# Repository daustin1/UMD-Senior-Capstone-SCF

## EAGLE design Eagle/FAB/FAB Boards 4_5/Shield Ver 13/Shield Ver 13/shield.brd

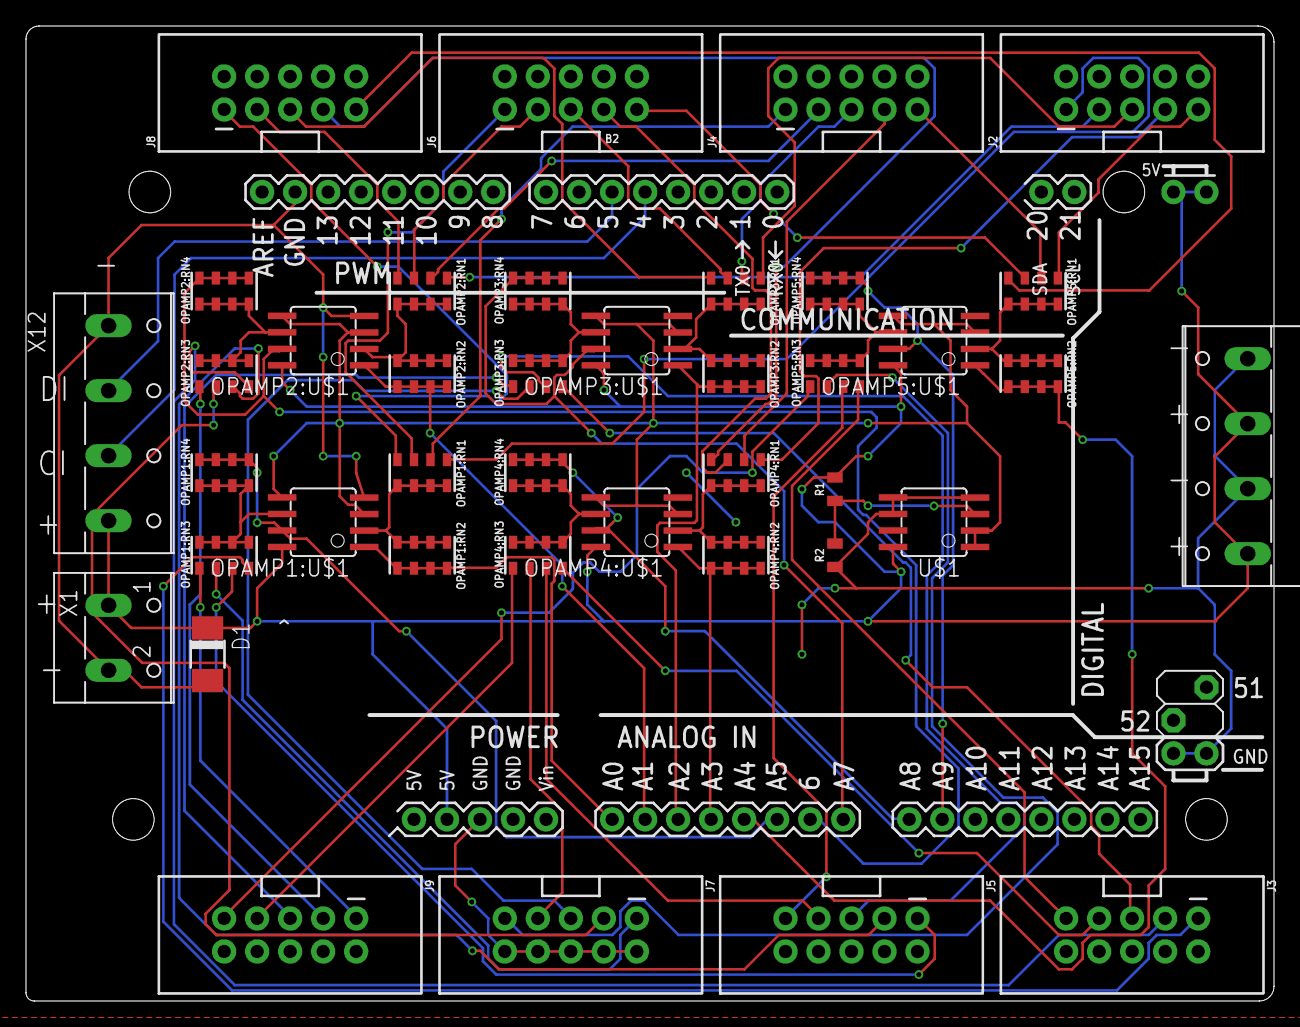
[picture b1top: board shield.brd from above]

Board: 2 copper layers, 96.0 x 75.0 mm, 41 parts (0 on the bottom side), 66 nets.

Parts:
B2: ARDUINO_MEGA_R3_EDITARDUINO_MEGA_EDIT; ARDUINO_MEGA_EDIT
D1: DO-214AC
J2, J3, J4, J5, J6, J7, J8, J9: AVR_SPI_PROG_5X2_NEWPTH2; 2X5-SHROUDED
OPAMP1:RN1, OPAMP1:RN2, OPAMP1:RN3, OPAMP1:RN4, OPAMP2:RN1, OPAMP2:RN2, OPAMP2:RN3, OPAMP2:RN4, OPAMP3:RN1, OPAMP3:RN2, OPAMP3:RN3, OPAMP3:RN4, OPAMP4:RN1, OPAMP4:RN2, OPAMP4:RN3, OPAMP4:RN4, OPAMP5:RN1, OPAMP5:RN2, OPAMP5:RN3, OPAMP5:RN4: 10k; 0805-ARV_EDIT10K
OPAMP1:U$1, OPAMP2:U$1, OPAMP3:U$1, OPAMP4:U$1, OPAMP5:U$1: MCP6002SMT; SOIC8
R1, R2: 1k; 0805
U$1: MCP6002SMT; SOIC8
X1: W237-102
X11, X12: W237-4

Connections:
+5V: B2.5V@0, B2.5V@1, B2.5V@2, D1.C, OPAMP1:U$1.8, OPAMP2:U$1.8, OPAMP3:U$1.8, OPAMP4:U$1.8, OPAMP5:U$1.8, R1.2, U$1.8, X1.1, X11.1, X11.3, X12.4
A1O: B2.A0, OPAMP1:RN2.5, OPAMP1:RN2.6, OPAMP1:RN2.7, OPAMP1:RN2.8, OPAMP1:U$1.1
A2O: B2.A1, OPAMP2:RN2.5, OPAMP2:RN2.6, OPAMP2:RN2.7, OPAMP2:RN2.8, OPAMP2:U$1.1
A3O: B2.A2, OPAMP3:RN2.5, OPAMP3:RN2.6, OPAMP3:RN2.7, OPAMP3:RN2.8, OPAMP3:U$1.1
A4O: B2.A3, OPAMP4:RN2.5, OPAMP4:RN2.6, OPAMP4:RN2.7, OPAMP4:RN2.8, OPAMP4:U$1.1
A5O: B2.A4, OPAMP5:RN2.5, OPAMP5:RN2.6, OPAMP5:RN2.7, OPAMP5:RN2.8, OPAMP5:U$1.1
A6O: B2.A5, OPAMP1:RN4.5, OPAMP1:RN4.6, OPAMP1:RN4.7, OPAMP1:RN4.8, OPAMP1:U$1.7
A7O: B2.A6, OPAMP2:RN4.5, OPAMP2:RN4.6, OPAMP2:RN4.7, OPAMP2:RN4.8, OPAMP2:U$1.7
A8O: B2.A7, OPAMP3:RN4.5, OPAMP3:RN4.6, OPAMP3:RN4.7, OPAMP3:RN4.8, OPAMP3:U$1.7
A9O: B2.A8, OPAMP4:RN4.5, OPAMP4:RN4.6, OPAMP4:RN4.7, OPAMP4:RN4.8, OPAMP4:U$1.7
A10O: B2.A9, OPAMP5:RN4.5, OPAMP5:RN4.6, OPAMP5:RN4.7, OPAMP5:RN4.8, OPAMP5:U$1.7
CI: B2.4, X12.3
DI: B2.5, X12.2
GND: B2.GND@0, B2.GND@1, B2.GND@2, B2.GND@3, B2.GND@4, D1.A, J2.2, J2.4, J2.6, J2.8, J2.10, J3.2, J3.4, J3.6, J3.8, J3.10, J4.2, J4.4, J4.6, J4.8, J4.10, J5.2, J5.4, J5.6, J5.8, J5.10, J6.2, J6.4, J6.6, J6.8, J6.10, J7.2, J7.4, J7.6, J7.8, J7.10, J8.2, J8.4, J8.6, J8.8, J8.10, J9.2, J9.4, J9.6, J9.8, J9.10, OPAMP1:U$1.4, OPAMP2:U$1.4, OPAMP3:U$1.4, OPAMP4:U$1.4, OPAMP5:U$1.4, R2.1, U$1.4, U$1.5, U$1.6, X1.2, X11.2, X11.4, X12.1
unnamed: R1.1, R2.2, U$1.3
OPAMP1:N$1: OPAMP1:RN3.5, OPAMP1:RN3.6, OPAMP1:RN3.7, OPAMP1:RN3.8, OPAMP1:RN4.1, OPAMP1:RN4.2, OPAMP1:RN4.3, OPAMP1:RN4.4, OPAMP1:U$1.6
OPAMP1:N$2: OPAMP1:RN1.5, OPAMP1:RN1.6, OPAMP1:RN1.7, OPAMP1:RN1.8, OPAMP1:RN2.1, OPAMP1:RN2.2, OPAMP1:RN2.3, OPAMP1:RN2.4, OPAMP1:U$1.2
OPAMP2:N$1: OPAMP2:RN3.5, OPAMP2:RN3.6, OPAMP2:RN3.7, OPAMP2:RN3.8, OPAMP2:RN4.1, OPAMP2:RN4.2, OPAMP2:RN4.3, OPAMP2:RN4.4, OPAMP2:U$1.6
OPAMP2:N$2: OPAMP2:RN1.5, OPAMP2:RN1.6, OPAMP2:RN1.7, OPAMP2:RN1.8, OPAMP2:RN2.1, OPAMP2:RN2.2, OPAMP2:RN2.3, OPAMP2:RN2.4, OPAMP2:U$1.2
OPAMP3:N$1: OPAMP3:RN3.5, OPAMP3:RN3.6, OPAMP3:RN3.7, OPAMP3:RN3.8, OPAMP3:RN4.1, OPAMP3:RN4.2, OPAMP3:RN4.3, OPAMP3:RN4.4, OPAMP3:U$1.6
OPAMP3:N$2: OPAMP3:RN1.5, OPAMP3:RN1.6, OPAMP3:RN1.7, OPAMP3:RN1.8, OPAMP3:RN2.1, OPAMP3:RN2.2, OPAMP3:RN2.3, OPAMP3:RN2.4, OPAMP3:U$1.2
OPAMP4:N$1: OPAMP4:RN3.5, OPAMP4:RN3.6, OPAMP4:RN3.7, OPAMP4:RN3.8, OPAMP4:RN4.1, OPAMP4:RN4.2, OPAMP4:RN4.3, OPAMP4:RN4.4, OPAMP4:U$1.6
OPAMP4:N$2: OPAMP4:RN1.5, OPAMP4:RN1.6, OPAMP4:RN1.7, OPAMP4:RN1.8, OPAMP4:RN2.1, OPAMP4:RN2.2, OPAMP4:RN2.3, OPAMP4:RN2.4, OPAMP4:U$1.2
OPAMP5:N$1: OPAMP5:RN3.5, OPAMP5:RN3.6, OPAMP5:RN3.7, OPAMP5:RN3.8, OPAMP5:RN4.1, OPAMP5:RN4.2, OPAMP5:RN4.3, OPAMP5:RN4.4, OPAMP5:U$1.6
OPAMP5:N$2: OPAMP5:RN1.5, OPAMP5:RN1.6, OPAMP5:RN1.7, OPAMP5:RN1.8, OPAMP5:RN2.1, OPAMP5:RN2.2, OPAMP5:RN2.3, OPAMP5:RN2.4, OPAMP5:U$1.2
S1A: J2.1, OPAMP1:RN1.1
S1B: J3.1, OPAMP1:RN3.4
S2A: J2.3, OPAMP2:RN1.1
S2B: J3.3, OPAMP2:RN3.4
S3A: J2.5, OPAMP3:RN1.1
S3B: J3.5, OPAMP3:RN3.4
S4A: J2.7, OPAMP4:RN1.1
S4B: J3.7, OPAMP4:RN3.4
S5A: J2.9, OPAMP5:RN1.1
S5B: J3.9, OPAMP5:RN3.4
S6A: J4.1, OPAMP1:RN1.2
S6B: J5.1, OPAMP1:RN3.3
S7A: J4.3, OPAMP2:RN1.2
S7B: J5.3, OPAMP2:RN3.3
S8A: J4.5, OPAMP3:RN1.2
S8B: J5.5, OPAMP3:RN3.3
S9A: J4.7, OPAMP4:RN1.2
S9B: J5.7, OPAMP4:RN3.3
S10A: J4.9, OPAMP5:RN1.2
S10B: J5.9, OPAMP5:RN3.3
S11A: J6.1, OPAMP1:RN1.3
S11B: J7.1, OPAMP1:RN3.2
S12A: J6.3, OPAMP2:RN1.3
S12B: J7.3, OPAMP2:RN3.2
S13A: J6.5, OPAMP3:RN1.3
S13B: J7.5, OPAMP3:RN3.2
S14A: J6.7, OPAMP4:RN1.3
S14B: J7.7, OPAMP4:RN3.2
S15A: J6.9, OPAMP5:RN1.3
S15B: J7.9, OPAMP5:RN3.2
S16A: J8.1, OPAMP1:RN1.4
S16B: J9.1, OPAMP1:RN3.1
S17A: J8.3, OPAMP2:RN1.4
S17B: J9.3, OPAMP2:RN3.1
S18A: J8.5, OPAMP3:RN1.4
S18B: J9.5, OPAMP3:RN3.1
S19A: J8.7, OPAMP4:RN1.4
S19B: J9.7, OPAMP4:RN3.1
S20A: J8.9, OPAMP5:RN1.4
S20B: J9.9, OPAMP5:RN3.1
VREF: OPAMP1:U$1.3, OPAMP1:U$1.5, OPAMP2:U$1.3, OPAMP2:U$1.5, OPAMP3:U$1.3, OPAMP3:U$1.5, OPAMP4:U$1.3, OPAMP4:U$1.5, OPAMP5:U$1.3, OPAMP5:U$1.5, U$1.1, U$1.2

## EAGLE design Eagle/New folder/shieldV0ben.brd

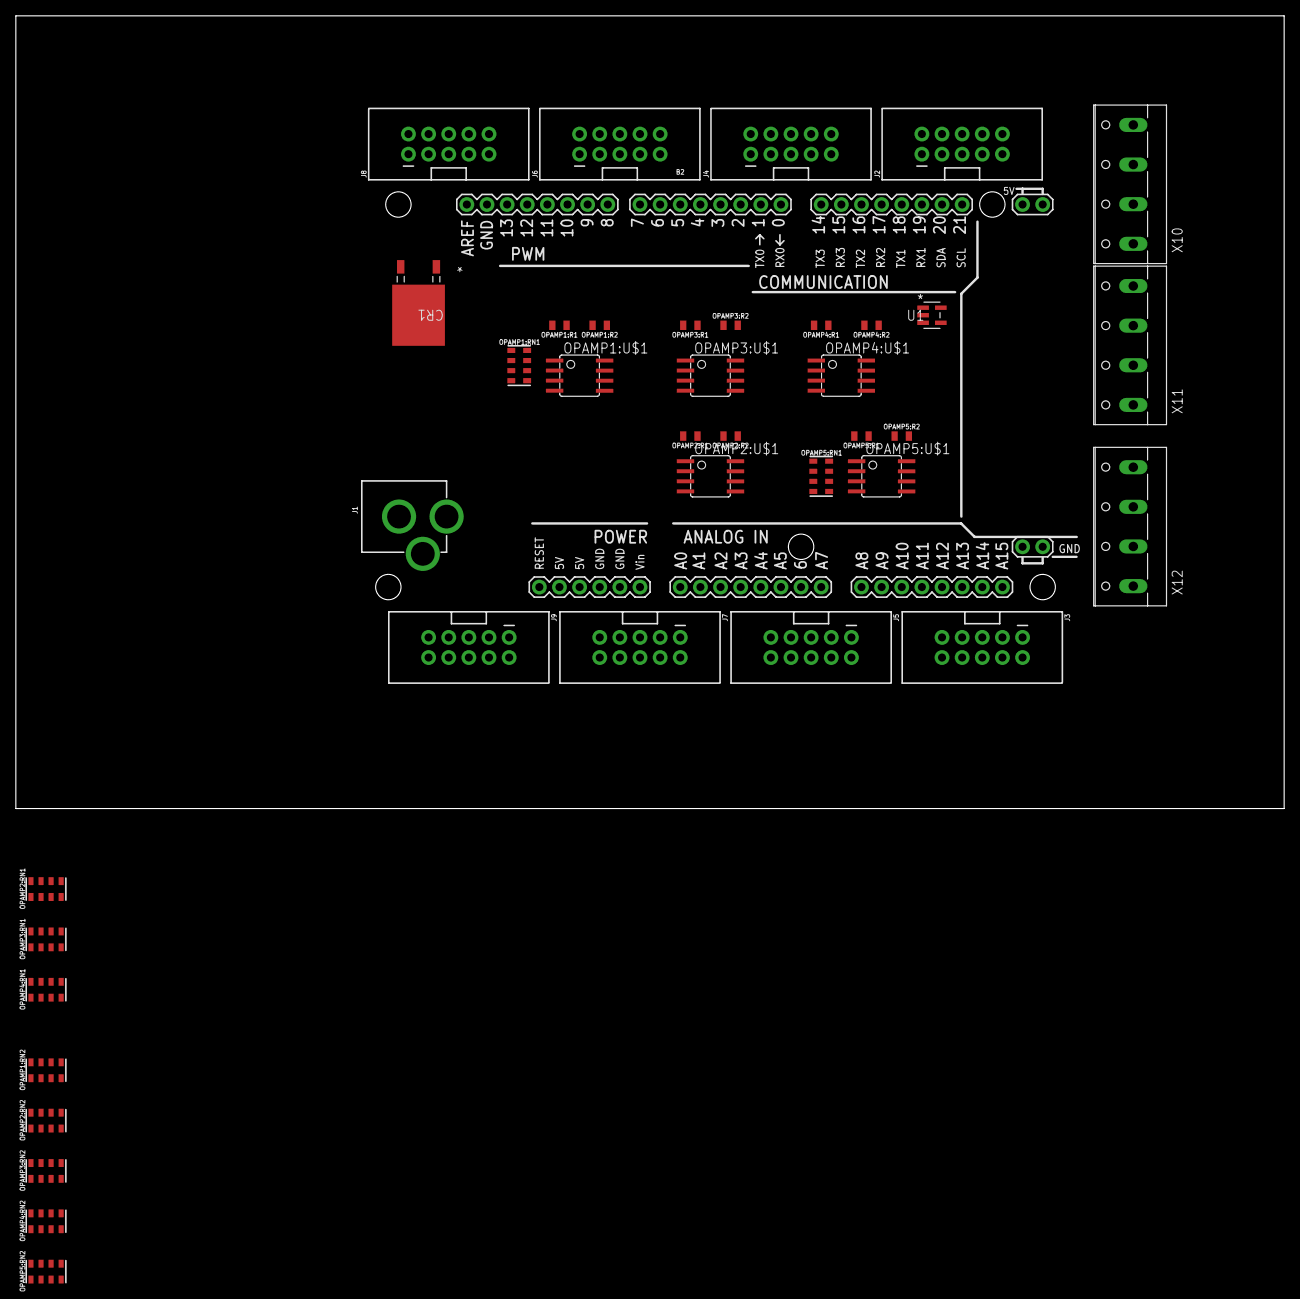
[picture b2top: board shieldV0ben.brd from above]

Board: 2 copper layers, 160.0 x 100.0 mm, 40 parts (0 on the bottom side), 66 nets, no tracks yet.

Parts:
B2: ARDUINO_MEGA_R3_EDIT; ARDUINO_MEGA_EDIT
CR1: L7805CDT-TR; DPAK
J1: POWER_JACK; POWER_JACK_PTH
J2, J3, J4, J5, J6, J7, J8, J9: AVR_SPI_PROG_5X2_NEWPTH2; 2X5-SHROUDED
OPAMP1:R1, OPAMP1:R2, OPAMP2:R1, OPAMP2:R2, OPAMP3:R1, OPAMP3:R2, OPAMP4:R1, OPAMP4:R2, OPAMP5:R1, OPAMP5:R2: 1k; 0805
OPAMP1:RN1, OPAMP1:RN2, OPAMP2:RN1, OPAMP2:RN2, OPAMP3:RN1, OPAMP3:RN2, OPAMP4:RN1, OPAMP4:RN2, OPAMP5:RN1, OPAMP5:RN2: 4k; 0805-ARV_EDIT
OPAMP1:U$1, OPAMP2:U$1, OPAMP3:U$1, OPAMP4:U$1, OPAMP5:U$1: MCP6002SMT; SOIC8
U1: TPS72101DBVT; DBV5
X10, X11, X12: W237-4

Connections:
5V: B2.VIN, CR1.2, U1.1, X10.1, X10.3, X11.1, X11.3, X12.4
A1O: B2.A0, OPAMP1:R1.2, OPAMP1:U$1.1
A2O: B2.A1, OPAMP2:R1.2, OPAMP2:U$1.1
A3O: B2.A2, OPAMP3:R1.2, OPAMP3:U$1.1
A6O: B2.A5, OPAMP1:R2.2, OPAMP1:U$1.7
A7O: B2.A6, OPAMP2:R2.2, OPAMP2:U$1.7
A8O: B2.A7, OPAMP3:R2.2, OPAMP3:U$1.7
A9O: B2.A8, OPAMP4:R2.2, OPAMP4:U$1.7
A10O: B2.A9, OPAMP5:R2.2, OPAMP5:U$1.7
CI: B2.4, X12.3
DI: B2.5, X12.2
GND: B2.GND@0, B2.GND@1, B2.GND@2, B2.GND@3, B2.GND@4, CR1.3, J1.GND, J1.GNDBREAK, J2.2, J2.4, J2.6, J2.8, J2.10, J3.2, J3.4, J3.6, J3.8, J3.10, J4.2, J4.4, J4.6, J4.8, J4.10, J5.2, J5.4, J5.6, J5.8, J5.10, J6.2, J6.4, J6.6, J6.8, J6.10, J7.2, J7.4, J7.6, J7.8, J7.10, J8.2, J8.4, J8.6, J8.8, J8.10, J9.2, J9.4, J9.6, J9.8, J9.10, OPAMP1:U$1.4, OPAMP2:U$1.4, OPAMP4:U$1.4, OPAMP5:U$1.4, U1.2, X10.2, X10.4, X11.2, X11.4, X12.1
OPAMP1:N$1: OPAMP1:R1.1, OPAMP1:RN1.5, OPAMP1:RN1.6, OPAMP1:RN1.7, OPAMP1:RN1.8, OPAMP1:U$1.2
OPAMP1:N$4: OPAMP1:R2.1, OPAMP1:RN2.5, OPAMP1:RN2.6, OPAMP1:RN2.7, OPAMP1:RN2.8, OPAMP1:U$1.6
OPAMP2:N$1: OPAMP2:R1.1, OPAMP2:RN1.5, OPAMP2:RN1.6, OPAMP2:RN1.7, OPAMP2:RN1.8, OPAMP2:U$1.2
OPAMP2:N$4: OPAMP2:R2.1, OPAMP2:RN2.5, OPAMP2:RN2.6, OPAMP2:RN2.7, OPAMP2:RN2.8, OPAMP2:U$1.6
OPAMP3:N$1: OPAMP3:R1.1, OPAMP3:RN1.5, OPAMP3:RN1.6, OPAMP3:RN1.7, OPAMP3:RN1.8, OPAMP3:U$1.2
OPAMP3:N$4: OPAMP3:R2.1, OPAMP3:RN2.5, OPAMP3:RN2.6, OPAMP3:RN2.7, OPAMP3:RN2.8, OPAMP3:U$1.6
OPAMP4:N$1: OPAMP4:R1.1, OPAMP4:RN1.5, OPAMP4:RN1.6, OPAMP4:RN1.7, OPAMP4:RN1.8, OPAMP4:U$1.2
OPAMP4:N$4: OPAMP4:R2.1, OPAMP4:RN2.5, OPAMP4:RN2.6, OPAMP4:RN2.7, OPAMP4:RN2.8, OPAMP4:U$1.6
OPAMP4:OUT: OPAMP4:R1.2, OPAMP4:U$1.1
OPAMP5:N$1: OPAMP5:R1.1, OPAMP5:RN1.5, OPAMP5:RN1.6, OPAMP5:RN1.7, OPAMP5:RN1.8, OPAMP5:U$1.2
OPAMP5:N$4: OPAMP5:R2.1, OPAMP5:RN2.5, OPAMP5:RN2.6, OPAMP5:RN2.7, OPAMP5:RN2.8, OPAMP5:U$1.6
OPAMP5:OUT: OPAMP5:R1.2, OPAMP5:U$1.1
OPAMP5:VREG: OPAMP5:U$1.3, OPAMP5:U$1.5
S1A: J2.1, OPAMP1:RN1.1
S1B: J3.1, OPAMP1:RN2.1
S2A: J2.3, OPAMP2:RN1.1
S2B: J3.3, OPAMP2:RN2.1
S3A: J2.5, OPAMP3:RN1.1
S3B: J3.5, OPAMP3:RN2.1
S4A: J2.7, OPAMP4:RN1.1
S4B: J3.7, OPAMP4:RN2.1
S5A: J2.9, OPAMP5:RN1.1
S5B: J3.9, OPAMP5:RN2.1
S6A: J4.1, OPAMP1:RN1.2
S6B: J5.1, OPAMP1:RN2.2
S7A: J4.3, OPAMP2:RN1.2
S7B: J5.3, OPAMP2:RN2.2
S8A: J4.5, OPAMP3:RN1.2
S8B: J5.5, OPAMP3:RN2.2
S9A: J4.7, OPAMP4:RN1.2
S9B: J5.7, OPAMP4:RN2.2
S10A: J4.9, OPAMP5:RN1.2
S10B: J5.9, OPAMP5:RN2.2
S11A: J6.1, OPAMP1:RN1.3
S11B: J7.1, OPAMP1:RN2.3
S12A: J6.3, OPAMP2:RN1.3
S12B: J7.3, OPAMP2:RN2.3
S13A: J6.5, OPAMP3:RN1.3
S13B: J7.5, OPAMP3:RN2.3
S14A: J6.7, OPAMP4:RN1.3
S14B: J7.7, OPAMP4:RN2.3
S15A: J6.9, OPAMP5:RN1.3
S15B: J7.9, OPAMP5:RN2.3
S16A: J8.1, OPAMP1:RN1.4
S16B: J9.1, OPAMP1:RN2.4
S17A: J8.3, OPAMP2:RN1.4
S17B: J9.3, OPAMP2:RN2.4
S18A: J8.5, OPAMP3:RN1.4
S19A: J8.7, OPAMP4:RN1.4
S19B: J9.7, OPAMP4:RN2.4
S20A: J8.9, OPAMP5:RN1.4
S20B: J9.9, OPAMP5:RN2.4
VCC: CR1.1, J1.PWR, OPAMP1:U$1.8, OPAMP2:U$1.8, OPAMP3:U$1.8, OPAMP4:U$1.8, OPAMP5:U$1.8, U1.3
VREG: OPAMP1:U$1.3, OPAMP1:U$1.5, OPAMP2:U$1.3, OPAMP2:U$1.5, OPAMP3:U$1.3, OPAMP3:U$1.5, OPAMP4:U$1.3, OPAMP4:U$1.5, U1.5

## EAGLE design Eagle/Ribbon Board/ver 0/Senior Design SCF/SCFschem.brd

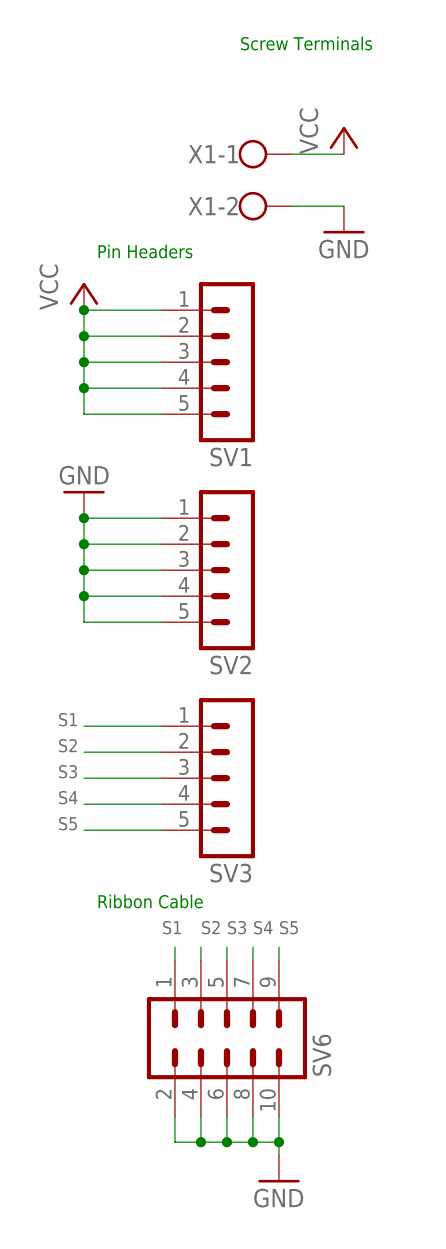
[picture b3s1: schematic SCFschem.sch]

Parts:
SV1, SV2, SV3: MA05-1
SV6: MA05-2
X1: 1X02_5MM_SCREW; W237-102

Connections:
GND: SV2.1, SV2.2, SV2.3, SV2.4, SV2.5, SV6.2, SV6.4, SV6.6, SV6.8, SV6.10, X1.2
S1: SV3.1, SV6.1
S2: SV3.2, SV6.3
S3: SV3.3, SV6.5
S4: SV3.4, SV6.7
S5: SV3.5, SV6.9
VCC: SV1.1, SV1.2, SV1.3, SV1.4, SV1.5, X1.1

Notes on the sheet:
Screw Terminals
Ribbon Cable
Pin Headers

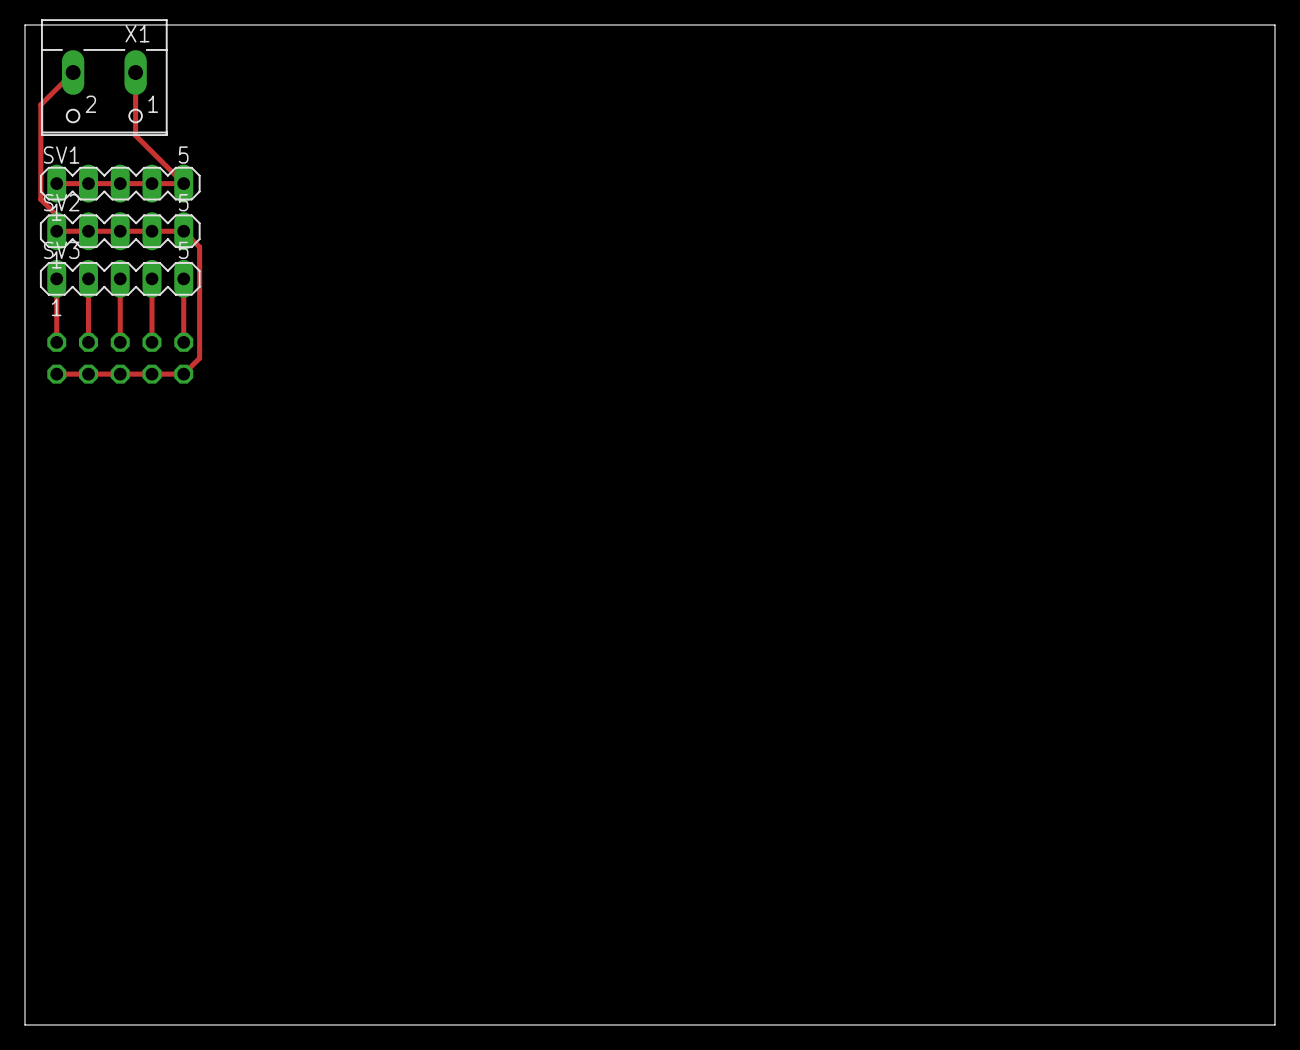
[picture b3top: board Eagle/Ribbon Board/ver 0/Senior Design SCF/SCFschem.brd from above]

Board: 2 copper layers, 100.0 x 80.0 mm, 5 parts (1 on the bottom side), 7 nets.

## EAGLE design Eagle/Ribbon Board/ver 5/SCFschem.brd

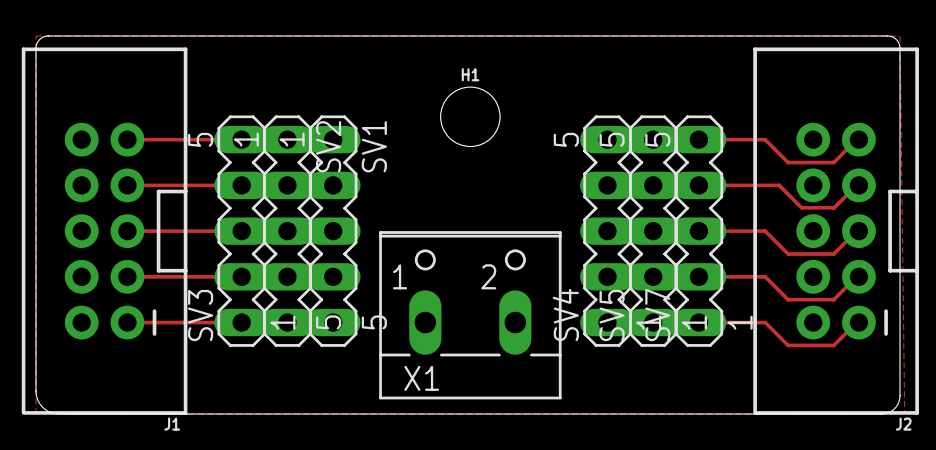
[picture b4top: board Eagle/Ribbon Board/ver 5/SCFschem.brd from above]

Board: 2 copper layers, 48.0 x 21.0 mm, 10 parts (0 on the bottom side), 12 nets.

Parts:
H1: STAND-OFF
J1, J2: AVR_SPI_PROG_5X2_NEWPTH2; 2X5-SHROUDED
SV1, SV2, SV3, SV4, SV5, SV7: MA05-1
X1: W237-102

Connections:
GND: J1.2, J1.4, J1.6, J1.8, J1.10, J2.2, J2.4, J2.6, J2.8, J2.10, SV2.1, SV2.2, SV2.3, SV2.4, SV2.5, SV5.1, SV5.2, SV5.3, SV5.4, SV5.5, X1.2
S1: J1.1, SV3.1
S2: J1.3, SV3.2
S3: J1.5, SV3.3
S4: J1.7, SV3.4
S5: J1.9, SV3.5
S6: J2.1, SV7.1
S7: J2.3, SV7.2
S8: J2.5, SV7.3
S9: J2.7, SV7.4
S10: J2.9, SV7.5
VCC: SV1.1, SV1.2, SV1.3, SV1.4, SV1.5, SV4.1, SV4.2, SV4.3, SV4.4, SV4.5, X1.1

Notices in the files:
parts and their libraries:
SparkFun-Boards: Licensing: Creative Commons ShareAlike 4.0 International - https://creativecommons.org/licenses/by-sa/4.0
